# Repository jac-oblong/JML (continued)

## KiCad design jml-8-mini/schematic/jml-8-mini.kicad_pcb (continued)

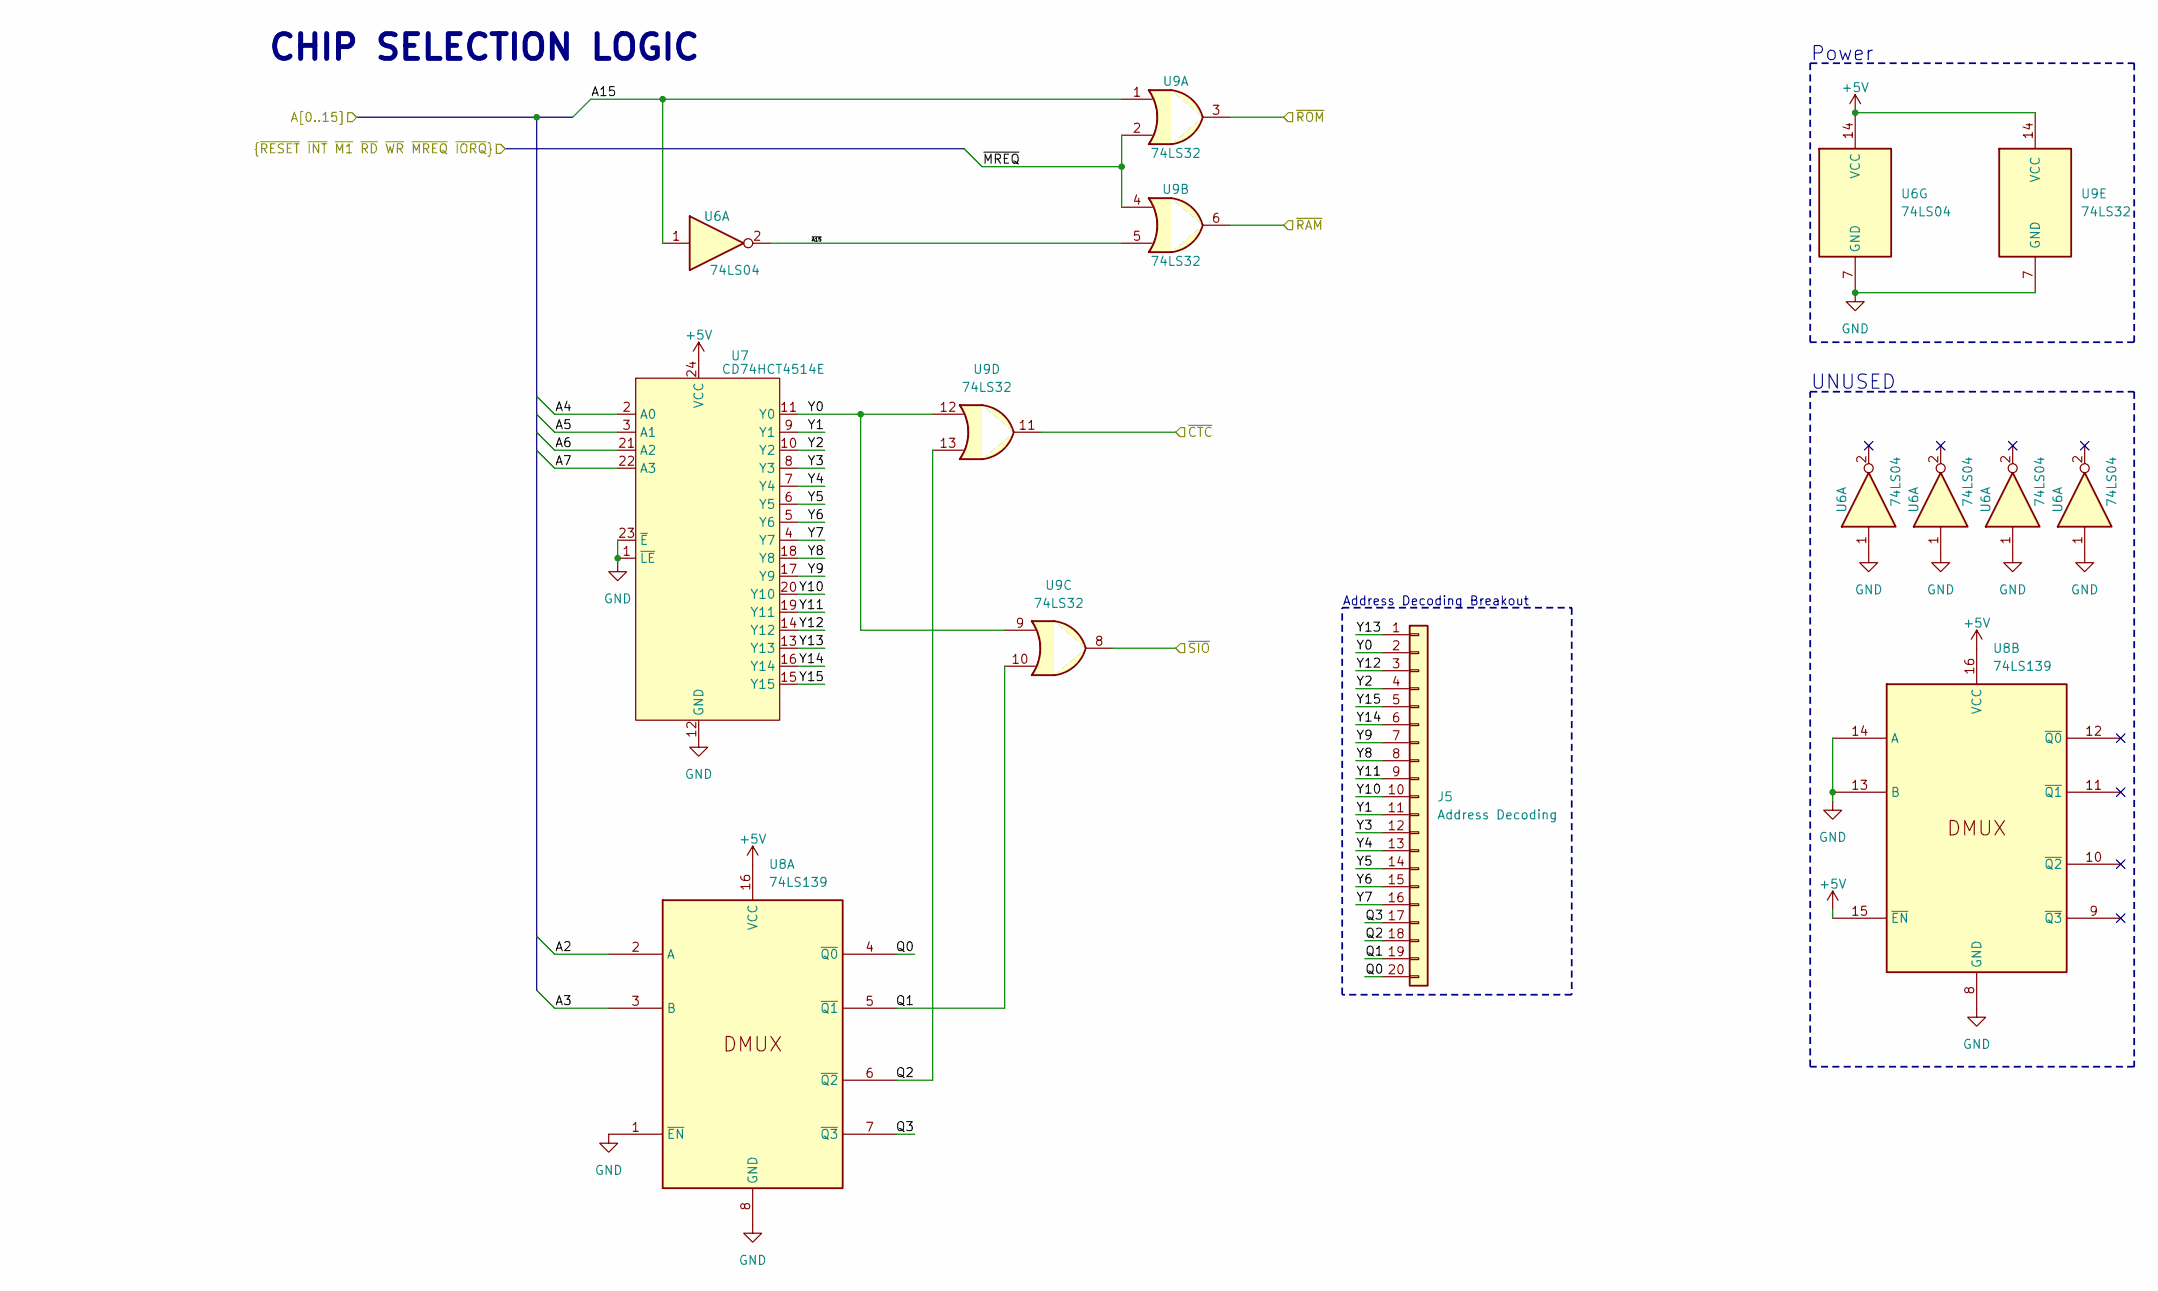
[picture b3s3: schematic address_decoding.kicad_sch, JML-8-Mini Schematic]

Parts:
J5: Address Decoding; PinHeader_1x20_P2.54mm_Vertical
U6: 74LS04; DIP-14_W7.62mm_Socket_LongPads
U7: CD74HCT4514E; DIP-24_W15.24mm_Socket_LongPads
U8: 74LS139; DIP-16_W7.62mm_Socket_LongPads
U9: 74LS32; DIP-14_W7.62mm_Socket_LongPads

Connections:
/A2: U8.2 (A); also elsewhere on the board
/A3: U8.3 (B); also elsewhere on the board
/A4: U7.2 (A0); also elsewhere on the board
/A5: U7.3 (A1); also elsewhere on the board
/A6: U7.21 (A2); also elsewhere on the board
/A7: U7.22 (A3); also elsewhere on the board
/Address Decoding/Q0: J5.20, U8.4 (~Q0)
/Address Decoding/Q1: J5.19, U8.5 (~Q1), U9.10
/Address Decoding/Q2: J5.18, U8.6 (~Q2), U9.13
/Address Decoding/Q3: J5.17, U8.7 (~Q3)
/Address Decoding/Y0: J5.2, U7.11 (Y0), U9.9, U9.12
/Address Decoding/Y1: J5.11, U7.9 (Y1)
/Address Decoding/Y2: J5.4, U7.10 (Y2)
/Address Decoding/Y3: J5.12, U7.8 (Y3)
/Address Decoding/Y4: J5.13, U7.7 (Y4)
/Address Decoding/Y5: J5.14, U7.6 (Y5)
/Address Decoding/Y6: J5.15, U7.5 (Y6)
/Address Decoding/Y7: J5.16, U7.4 (Y7)
/Address Decoding/Y8: J5.8, U7.18 (Y8)
/Address Decoding/Y9: J5.7, U7.17 (Y9)
/Address Decoding/Y10: J5.10, U7.20 (Y10)
/Address Decoding/Y11: J5.9, U7.19 (Y11)
/Address Decoding/Y12: J5.3, U7.14 (Y12)
/Address Decoding/Y13: J5.1, U7.13 (Y13)
/Address Decoding/Y14: J5.6, U7.16 (Y14)
/Address Decoding/Y15: J5.5, U7.15 (Y15)
/~CTC: U9.11; also elsewhere on the board
/~MREQ: U9.2, U9.4; also elsewhere on the board
/~RAM: U9.6; also elsewhere on the board
/~ROM: U9.3; also elsewhere on the board
/~SIO: U9.8; also elsewhere on the board

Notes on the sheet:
Address Decoding Breakout
UNUSED
Power
CHIP SELECTION LOGIC

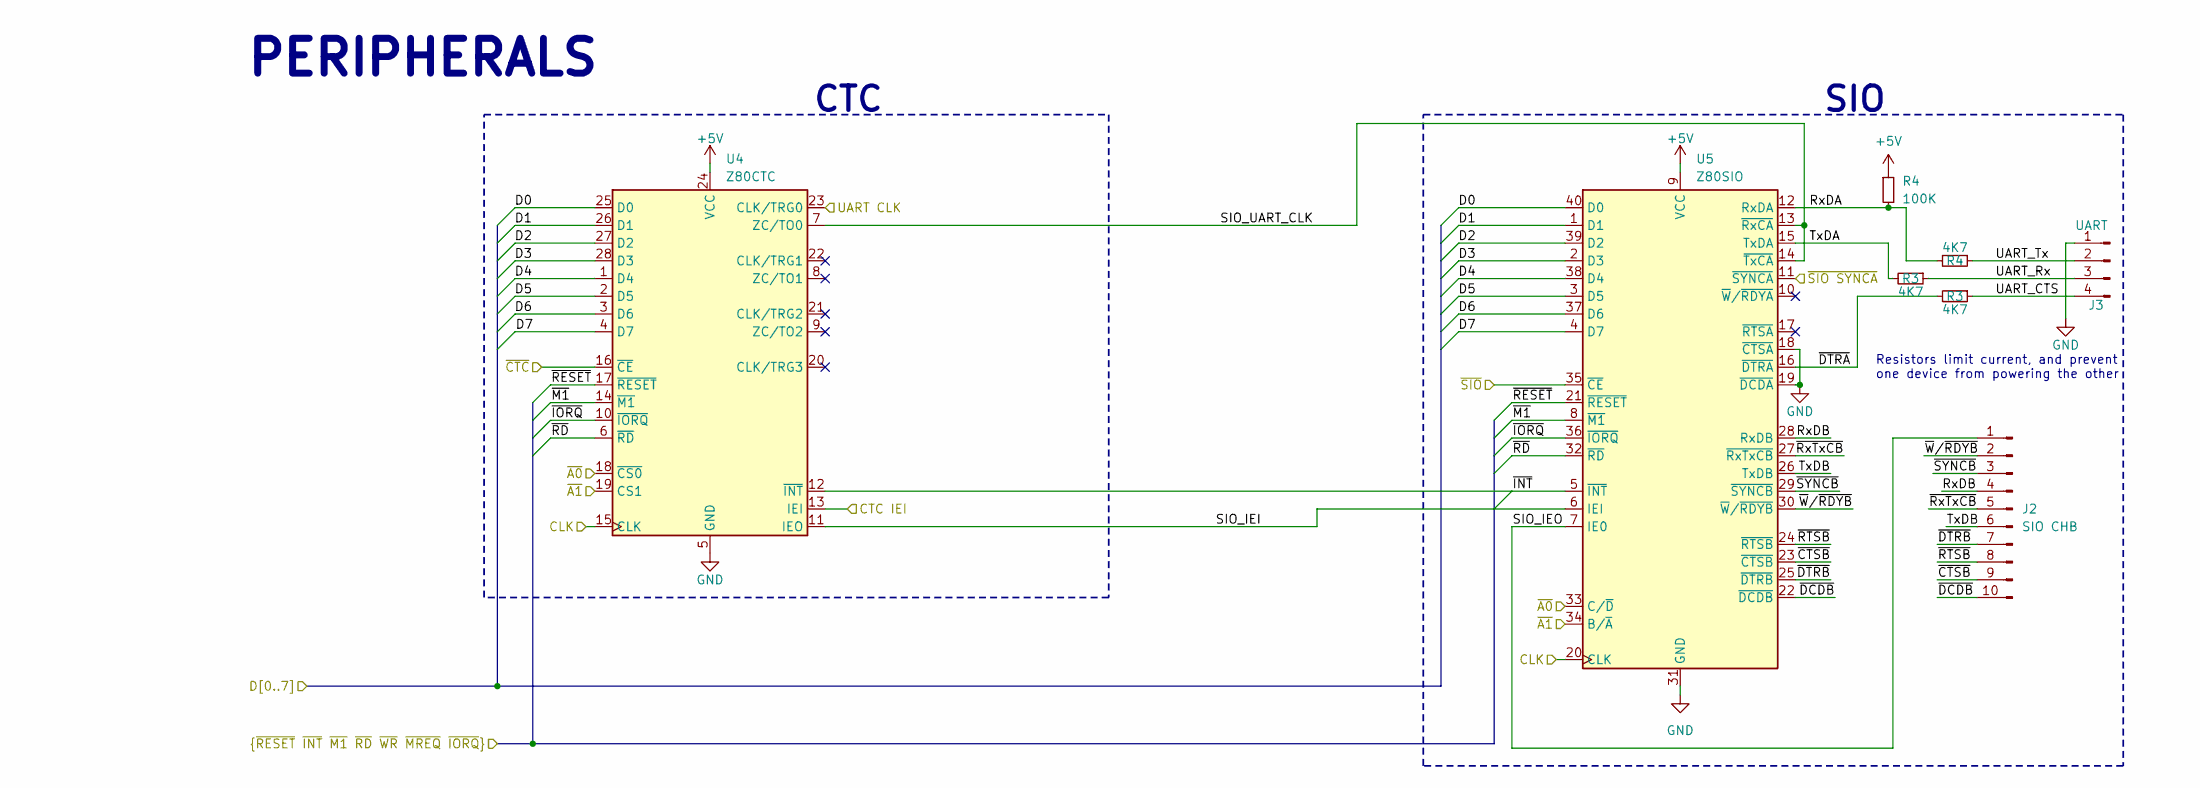
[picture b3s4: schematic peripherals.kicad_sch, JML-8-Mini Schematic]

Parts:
J2: SIO CHB; PinHeader_1x10_P2.54mm_Vertical
J3: UART; PinHeader_1x04_P2.54mm_Horizontal
R3, R4: 4K7; R_Axial_DIN0207_L6.3mm_D2.5mm_P7.62mm_Horizontal
U4: Z80CTC; DIP-28_W15.24mm_Socket_LongPads
U5: Z80SIO; DIP-40_W15.24mm_Socket_LongPads

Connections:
/A0: U4.18 (~CS0), U5.33 (C/~D); also elsewhere on the board
/A1: U4.19 (CS1), U5.34 (B/~A); also elsewhere on the board
/CLK: U4.15 (CLK), U5.20 (CLK); also elsewhere on the board
/CTC IEI: U4.13 (IEI); also elsewhere on the board
/D0: U4.25 (D0), U5.40 (D0); also elsewhere on the board
/D1: U4.26 (D1), U5.1 (D1); also elsewhere on the board
/D2: U4.27 (D2), U5.39 (D2); also elsewhere on the board
/D3: U4.28 (D3), U5.2 (D3); also elsewhere on the board
/D4: U4.1 (D4), U5.38 (D4); also elsewhere on the board
/D5: U4.2 (D5), U5.3 (D5); also elsewhere on the board
/D6: U4.3 (D6), U5.37 (D6); also elsewhere on the board
/D7: U4.4 (D7), U5.4 (D7); also elsewhere on the board
/Peripherals/RxDA: R4.2, U5.12 (RxDA); also elsewhere on the board
/Peripherals/RxDB: J2.4, U5.28 (RxDB)
/Peripherals/SIO_IEI: U4.11 (IEO), U5.6 (IEI)
/Peripherals/SIO_IEO: J2.1, U5.7 (IE0)
/Peripherals/SIO_UART_CLK: U4.7 (ZC/TO0), U5.13 (~RxCA), U5.14 (~TxCA)
/Peripherals/TxDB: J2.6, U5.26 (TxDB)
/Peripherals/UART CLK: U4.23 (CLK/TRG0); also elsewhere on the board
/Peripherals/~CTSB: J2.9, U5.23 (~CTSB)
/Peripherals/~DCDB: J2.10, U5.22 (~DCDB)
/Peripherals/~DTRB: J2.7, U5.25 (~DTRB)
/Peripherals/~RTSB: J2.8, U5.24 (~RTSB)
/Peripherals/~RxTxCB: J2.5, U5.27 (~RxTxCB)
/Peripherals/~SYNCB: J2.3, U5.29 (~SYNCB)
/Peripherals/~W/~RDYB: J2.2, U5.30 (~W/~RDYB)
/~CTC: U4.16 (~CE); also elsewhere on the board
/~INT: U4.12 (~INT), U5.5 (~INT); also elsewhere on the board
/~IORQ: U4.10 (~IORQ), U5.36 (~IORQ); also elsewhere on the board
/~M1: U4.14 (~M1), U5.8 (~M1); also elsewhere on the board
/~RD: U4.6 (~RD), U5.32 (~RD); also elsewhere on the board
/~SIO SYNCA: U5.11 (~SYNCA); also elsewhere on the board
/~SIO: U5.35 (~CE); also elsewhere on the board

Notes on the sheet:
Resistors limit current, and prevent one device from powering the other
CTC
SIO
PERIPHERALS

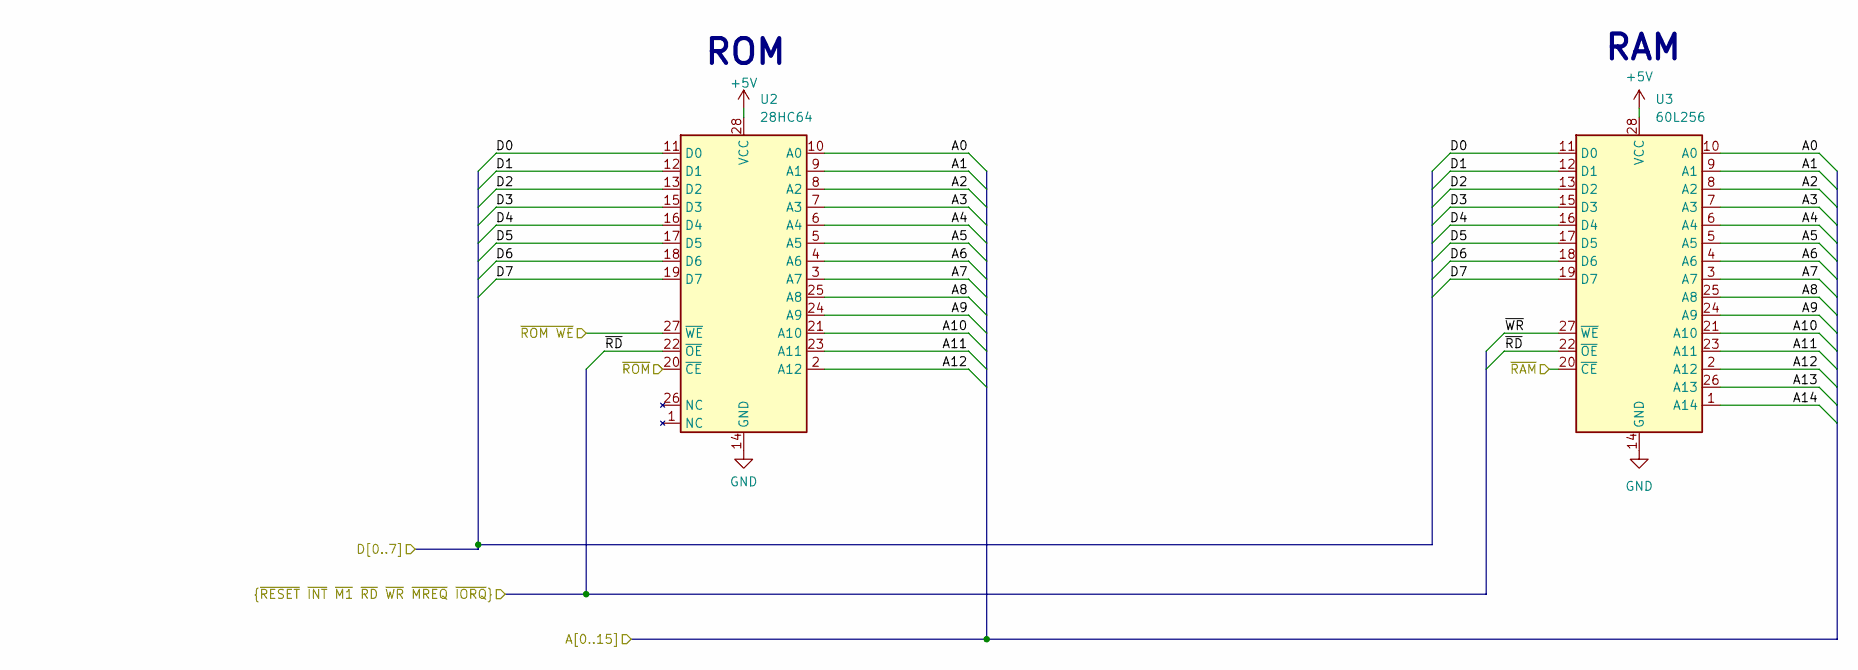
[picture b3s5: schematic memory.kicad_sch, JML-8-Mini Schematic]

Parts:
U2: 28HC64; DIP-28_W15.24mm_Socket_LongPads
U3: 60L256; DIP-28_W15.24mm_Socket_LongPads

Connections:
/A0: U2.10 (A0), U3.10 (A0); also elsewhere on the board
/A1: U2.9 (A1), U3.9 (A1); also elsewhere on the board
/A2: U2.8 (A2), U3.8 (A2); also elsewhere on the board
/A3: U2.7 (A3), U3.7 (A3); also elsewhere on the board
/A4: U2.6 (A4), U3.6 (A4); also elsewhere on the board
/A5: U2.5 (A5), U3.5 (A5); also elsewhere on the board
/A6: U2.4 (A6), U3.4 (A6); also elsewhere on the board
/A7: U2.3 (A7), U3.3 (A7); also elsewhere on the board
/A8: U2.25 (A8), U3.25 (A8); also elsewhere on the board
/A9: U2.24 (A9), U3.24 (A9); also elsewhere on the board
/A10: U2.21 (A10), U3.21 (A10); also elsewhere on the board
/A11: U2.23 (A11), U3.23 (A11); also elsewhere on the board
/A12: U2.2 (A12), U3.2 (A12); also elsewhere on the board
/A13: U3.26 (A13); also elsewhere on the board
/A14: U3.1 (A14); also elsewhere on the board
/D0: U2.11 (D0), U3.11 (D0); also elsewhere on the board
/D1: U2.12 (D1), U3.12 (D1); also elsewhere on the board
/D2: U2.13 (D2), U3.13 (D2); also elsewhere on the board
/D3: U2.15 (D3), U3.15 (D3); also elsewhere on the board
/D4: U2.16 (D4), U3.16 (D4); also elsewhere on the board
/D5: U2.17 (D5), U3.17 (D5); also elsewhere on the board
/D6: U2.18 (D6), U3.18 (D6); also elsewhere on the board
/D7: U2.19 (D7), U3.19 (D7); also elsewhere on the board
/~RAM: U3.20 (~CE); also elsewhere on the board
/~RD: U2.22 (~OE), U3.22 (~OE); also elsewhere on the board
/~ROM WE: U2.27 (~WE); also elsewhere on the board
/~ROM: U2.20 (~CE); also elsewhere on the board
/~WR: U3.27 (~WE); also elsewhere on the board

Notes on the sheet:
RAM
ROM

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
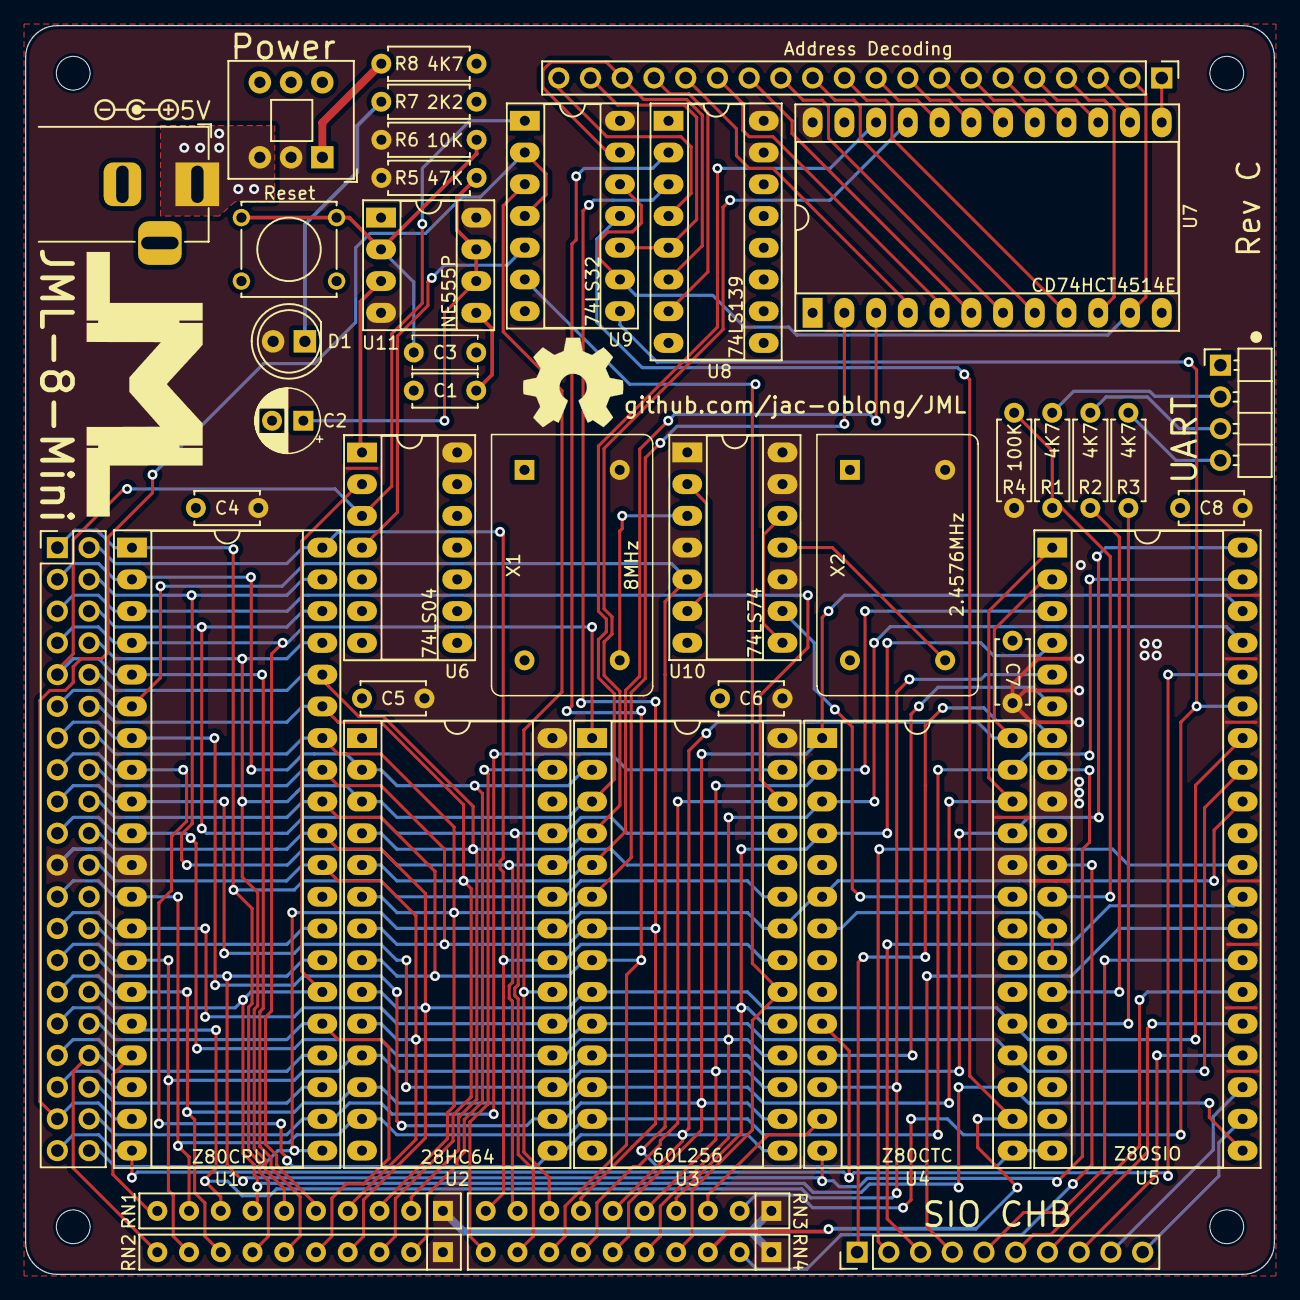
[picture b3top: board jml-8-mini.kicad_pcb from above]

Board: 4 copper layers, 99.9 x 99.9 mm, 45 parts (0 on the bottom side), 98 nets.

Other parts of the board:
R1, R2: 4K7; R_Axial_DIN0207_L6.3mm_D2.5mm_P7.62mm_Horizontal

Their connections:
/Peripherals/RxDA: R1.2; also elsewhere on the board

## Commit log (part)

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2023-05-29 Create folder for reading keyboard scan codes with Arduino
2023-05-30 simple script testing hardware functionality
2023-05-30 rewrite code a bit to allow keyboard to respond properly
2023-05-31 initial version of code to reset keyboard
2023-06-08 print out more information for debugging keyboard interface
2023-06-08 began working on programs for jml-XX computers
2023-06-09 starting over with the basics, make sure able to prompt a clock package
2023-06-10 update README, final version of arduino code
2023-06-10 update README to include links to helpful information about keyboard
2023-06-11 download mcu datasheet
2023-06-13 download more datasheets
2023-06-14 write READMEs for assemblers
2023-06-15 update README with more information
2023-06-15 small update to README
2023-06-16 insert all instructions, their opcodes and arguments
2023-06-16 add functionality for syntax errors, fix but with not returning opcode properly
2023-06-17 change README to reflext how assembler works, implement more of assembler
2023-06-18 update how label syntax works
2023-06-19 implement .org functionality
2023-06-19 implement .label and .const functionality
2023-06-19 handle variables in .org
2023-06-20 implement constant arrays
2023-06-20 complete pic assembler, remains untested
2023-06-21 begin testing, fix various bugs
2023-06-21 include .gitignore in repo
2023-06-21 create more tests, fix more bugs
2023-06-21 fix more bugs
2023-06-21 fix some more bugs
2023-06-21 get started on new version of assembler
2023-06-22 more work on new assembler
2023-06-22 implement instruction funcitonality for assembler v2
2023-06-22 finish implementing pic assembler v2, need to test & debug
2023-06-22 basic instructions using decimal numbers tested and confirmed
2023-06-22 convert decimal tests to hex and binary
2023-06-22 remove original version of pic assembler, v2 still needs debugging
2023-06-22 most of bugs with hex and binary numbers solved, still some issues
2023-06-22 fix problem with differences between decimal/hexadecimal/binary
2023-06-22 remove unnecessary info
2023-06-22 fix error with not ignoring empty line
2023-06-22 test using constants, work successfully
2023-06-22 testing constant arrays, not working yet
2023-06-23 fix errors with constant arrays
2023-06-23 fix error handling going wrong, make labels point to right location, make sure not writing outside bounds of file
2023-06-23 fix problem with '_' in labels/constants testing using numbers in labels/constants
2023-06-23 more checking of variables, problem with numbers in labels/constants was due to typo in test file
2023-06-23 fix errors with bit shifting <d> arg
2023-06-23 make sure size of file is accurate
2023-06-23 begin implement .data
2023-06-23 implement .data, add to README, test functionality
2023-06-24 create platformio project for uploading to PIC
2023-06-24 begin implementing pic programmer
2023-06-24 Create LICENSE
2023-06-25 figure out how to upload file to Arduino
2023-06-26 continue working on programmer
2023-06-26 more work on programmer
2023-06-26 complete programmer?
2023-06-26 fewer instructions, making use of carry out flag
2023-06-27 include z80 datasheet
2023-06-27 update datasheets readme
2023-06-28 fix some typos
2023-06-28 can read from memory
2023-07-01 updates to project
2023-07-03 add more to logisim
2023-07-04 change misspelled names
2023-07-05 initial work on fpga implementation
2023-07-05 more updates to fpga design
2023-07-06 create receiver module for getting message
2023-07-06 update receiver to work better
2023-07-06 more work on keyboard interface
2023-07-06 adding more documentation
2023-07-08 specify outputs to fix some errors
2023-07-13 specify inputs in order to fix error
2023-07-16 beginning to work on arduino debugger for z80
2023-07-17 reorganize some stuff
2023-07-17 update z80-debugger
2023-07-17 remove this stupid folder
2023-07-20 change how counter works
2023-07-20 change initial_response somewhat, add test
2023-07-20 testing initial response module
2023-07-20 update makefile for testing
2023-07-20 relocate some files, fix formatting on message_decoder
2023-07-20 make receiver tests
2023-07-20 reformat receiver
2023-07-20 fix errors
2023-07-20 fix errors in receiver
2023-07-20 testing results
2023-07-20 move file
2023-07-20 organize and clean
2023-07-20 receiver waveform test
2023-07-21 fix typo
2023-07-21 update testfile
2023-07-22 run test of receiver and fix some bugs
2023-07-22 run test on reseting keyboard, fix some bugs
2023-07-22 update toplevel to test resetting keyboard
2023-07-22 add some more datasheets
2023-07-22 remove rst
2023-07-22 create IO constraints
2023-07-22 fix additional errors
2023-07-22 update datasheets
2023-07-22 remove unnecessary datasheets
2023-07-22 remove file, starting from scratch
2023-07-22 rename file
2023-07-22 more datasheets
2023-07-23 get resetting of keyboard working
2023-07-23 remove this unneeded file
2023-07-24 rerun receiver test
2023-07-24 add more functionality to receiver
2023-07-24 start implementing the message_decoder
2023-07-24 further implementation of message decoder
2023-07-24 format md file more nicely
2023-07-25 reorganize a little, implement more of message decoder
2023-07-26 add shift section
2023-07-26 add more to message_decoder
2023-07-26 start on cpu interface for keyboard
2023-07-26 start working on ram tester
2023-07-27 script to test ram chips
2023-07-27 finish ram-tester (kinda), add to README
2023-07-27 fix a quick bug
2023-07-30 update datasheet
2023-08-02 begin implementing rom-reader
2023-08-29 rename some files
2023-08-29 finish arduino program for rom utilities
2023-08-29 add more documentation for the project
2023-08-30 start creating schematic for rom-utilities
2023-08-30 change some of the pins around
2023-08-30 finishing touches to rom-utilities, starting on ui
2023-08-31 update documentation
2023-08-31 more work on ui, only need to implent few more functions
2023-08-31 more work on rom-utilities-ui
2023-08-31 update ui documentation
2023-08-31 finish implementation of rom-utilities-ui
2023-08-31 wait for Arduino to signal to proceed
2023-09-02 some formatting changes, other minor changes in search of bug
2023-09-02 update documentation to add warning about incompatible HIGH levels
2023-09-02 fix ppins being wrong
2023-09-03 random stuff, probably will not work
2023-09-04 remove unnecessary project
2023-09-04 remove these files, no longer relevant to project
2023-09-04 remove some unnecessary things
2023-09-07 begin working on schematic for jml-8 mini
2023-09-09 updates to jml-8 mini schematic
2023-09-11 schematic stuff, simple test of current state of computer
2023-09-11 actually do what i wanted to do in test
2023-09-12 update schematic, new program to test RAM
2023-09-12 some minor changes to ram tester
2023-09-13 small script to test RAM
2023-09-20 ignore some more files/projects
2023-09-22 updates to schematics
2023-09-22 lots of updates to jml-8 mini 'os'
2023-09-23 many changes to schematic to make more organized
2023-09-24 lots of changes to schematic, redone to make easier to read and add to
2023-09-25 updates to schematic, generally making formatting better
2023-09-25 initial code to set up ctc & sio, does not transfer data yet
2023-09-26 reformatting of code, testing sending all characters over uart
2023-09-27 testing sending characters from jml-8-mini to computer
2023-09-28 add more documentation
2023-09-28 make sure to actually zero out data in mem
2023-09-28 throw away new memory if not had time to handle old mem
2023-09-28 add a makefile for project
2023-09-28 some formatting changes, renaming of variables, better documentation
2023-09-28 'main' code will now receive byte, increment value, and send back
2023-10-01 minor updates to schematic
2023-10-01 fix bug in makefile, clean before assembling
2023-10-03 complete schematic
2023-10-03 more things to ignore
2023-10-03 add to info section of schematic
2023-10-05 updates to some READMEs in order to keep them accurate
2023-10-05 update info section of schematic
2023-10-05 add mounting holes for PCB
2023-10-05 general "neatening" of schematics
2023-10-06 change some footprints
2023-10-06 change more footprints
2023-10-06 add resistor so caps discharge slower when power cuts off
2023-10-06 more stuff "yay"
2023-10-06 swap pins on resistor network for easier pcb connection
2023-10-06 idk what this is, it just keeps happening?
2023-10-07 updates to READMEs
2023-10-07 links to each family/model
2023-10-07 fix links
2023-10-07 actually fix links
2023-10-09 lots of updates to schematic to make pcb routing easier, start on pcb design
2023-10-10 making pcb 4 layers instead of 2, restarting routing, more exact outline dimensions
2023-10-12 complete PCB routing
2023-10-12 fix wrong label, add labels and figures to pcb
2023-10-13 created JML logo
2023-10-13 more versions of logo
2023-10-13 add JML logo to pcb
2023-10-14 new symbol & footprint for logo, add to schematic and pcb
2023-10-16 create gerbers for pcb
2023-10-16 updates to gerber files
2023-10-16 fix some errors in schematic/pcb
2023-10-16 regenerate gerbers
2023-10-16 add zip file for gerbers
2023-10-16 updates to silkscreen, regenerate gerbers
2023-10-17 add ground plane to top and bottom, fix silkscreen, regenerate gerbers
2023-10-18 rename folder
2023-10-18 change "JML-8 Mini" to "JML-8-Mini" in schematic description
2023-10-18 minor changes to ground plane on front and back layer, regenerate gerbers
2023-10-21 remove CTC header pins, start Rev B
2023-10-21 Rev B, change dimensions of PCB for reduced cost
2023-10-22 more updates for new PCB design
2023-10-23 regenerate gerbers for Rev B PCB
2023-10-23 change layers 2 & 3 to GND and put PWR on top and bottom, regenerate gerbers
2023-10-29 move files around for better ordering, split single assembly file into multiple
2023-10-29 current version of firmware, echos character in complex way
2023-10-29 fix some bugs with rx buffer
2023-11-06 more things to ignore, yay!!!
2023-11-06 change firmware to work more easily with BASIC (lots of simplifications)
2023-11-06 fix incorrect value for resistor
2023-11-06 create REV C with new changes, update gerbers
2023-11-06 update README to have more accurate documentation on JML-8-Mini
2023-11-06 no longer making custom terminal
2023-11-08 PCB image and schematic pdf
2023-11-08 update firmware to have monitor program
2023-11-09 start working on case for jml-8-mini
2023-11-10 add origin to pcb file
2023-11-10 get better 3d model of switch
2023-11-10 import pcb step file into case design
2023-11-14 update some documentation
2023-11-14 update docs
2023-11-14 more doc updates
2023-11-19 finish jml-8-mini case
2023-11-19 logo stuff
2023-11-19 more docs
2023-11-19 fix some errors in memory monitor, bugs still present (read & write untested)
2023-11-20 complete jml-8-mini firmware
2023-11-24 lots more docs
2023-11-24 fix typo in docs
2023-11-30 add some example programs for JML-8-Mini
2023-12-15 begin working on JML-6502-Mini schematic
2023-12-17 complete jml-6502-mini schematic
2024-01-14 begin working on pcb for jml-6502-mini
2024-01-14 brief overview of purpose of branch
2024-01-14 abandon JML-6502-Mini
2024-01-14 Revert "abandon JML-6502-Mini", wrong branch
    This reverts commit 3f1e0d8104f483ad7bf20c2ba9d51af5e8cfbfc4.
2024-01-14 abandon JML-6502-Mini model
2024-01-21 add new kicad library parts
2024-01-21 create schematic and pcb for jml-8-mini VGA daughterboard
2024-01-23 add address decoding circuitry, regenerate gerbers
2024-01-23 create pdf of schematic
2024-01-24 add README for vga interface
2024-01-27 add to gitignore
2024-01-28 create basic FPGA-based VGA display
2024-01-29 add video ram and make character generation more sophisticated
2024-02-01 show all characters
2024-02-11 major redesign of vga signal generation
2024-02-11 minor update to videoram.txt generation script
2024-02-12 new pattern
2024-02-13 add new module that handles interfacing with z80
2024-03-07 switching back to old way for video ram
2024-03-08 don't do the message file thing, it was dumb
2024-03-09 lots of changes to design (again), still needs some bugs fixed
2024-03-12 some debugging work, not complete yet
